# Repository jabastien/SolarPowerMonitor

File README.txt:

I'm building an Arduino Solar Power Monitor for my small home solar power system. At this point, I have 245 watts of solar panels.

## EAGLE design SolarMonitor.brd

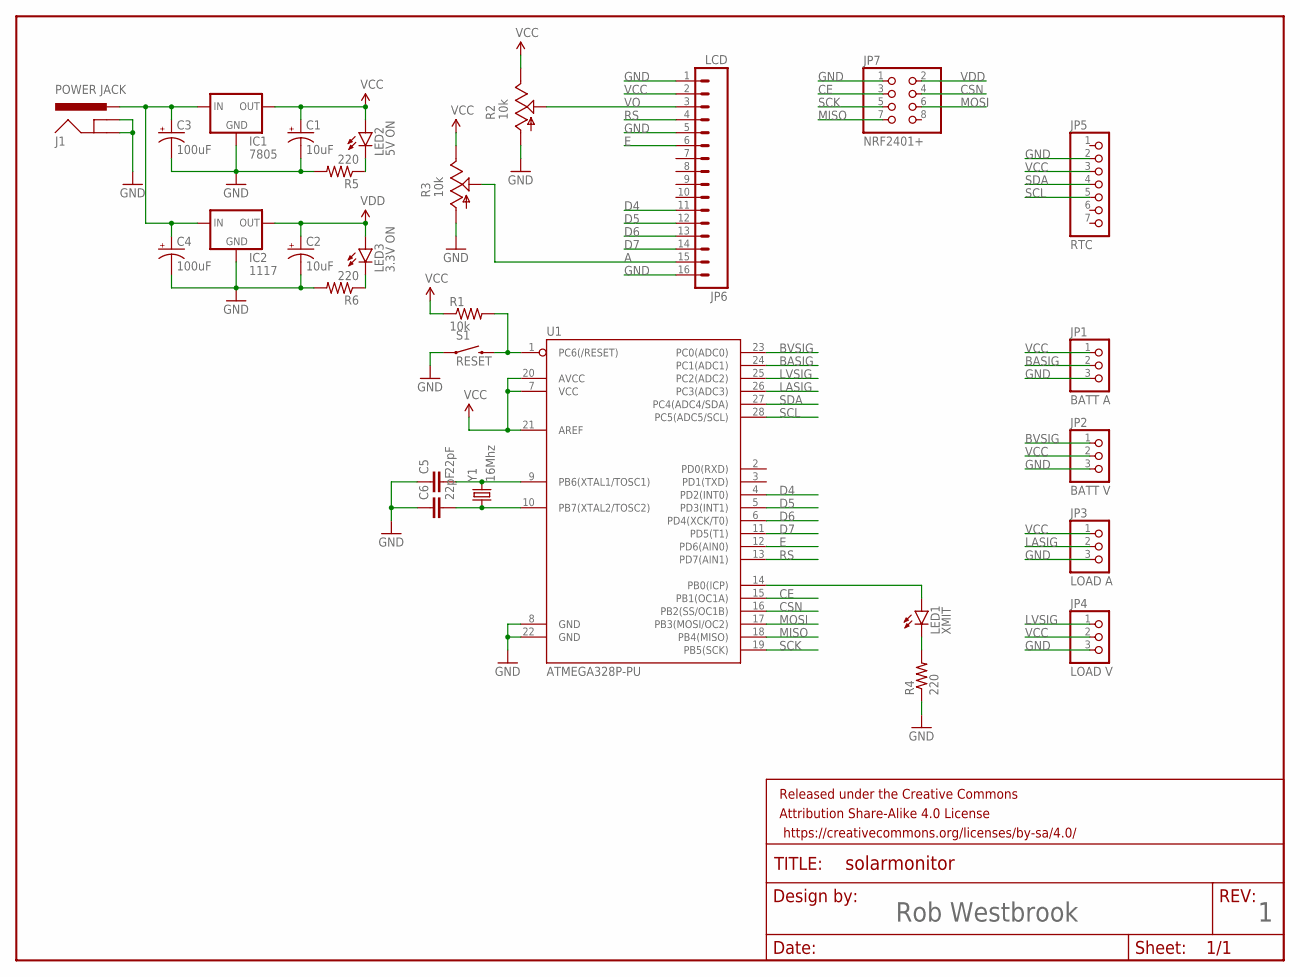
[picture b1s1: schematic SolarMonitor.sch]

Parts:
C1, C2: 10uF; CPOL-RADIAL-100UF-25V
C3, C4: 100uF; CPOL-RADIAL-10UF-25V
C5, C6: 22pF; CAP-PTH-SMALLEZ
FRAME1: FRAME-LETTER; CREATIVE_COMMONS
IC1: 7805; TO-220-ALT
IC2: 1117; 78XXL
J1: POWER JACK; POWER_JACK_PTH
JP1: BATT A; 1X03
JP2: BATT V; 1X03
JP3: LOAD A; 1X03
JP4: LOAD V; 1X03
JP5: RTC; 1X07
JP6: LCD; 1X16_LOCK
JP7: NRF2401+; 2X04
LED1: XMIT; LED5MM
LED2: 5V ON; LED5MM
LED3: 3.3V ON; LED5MM
R1: 10k; AXIAL-0.4
R2, R3: 10k; S64W
R4, R5, R6: 220; AXIAL-0.4
S1: RESET; TACTILE-PTH
U1: ATMEGA328P-PU; DIL28-3
Y1: 16Mhz; HC49US

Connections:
A: JP6.15, R3.S
BASIG: JP1.2, U1.24 (PC1(ADC1))
BVSIG: JP2.1, U1.23 (PC0(ADC0))
CE: JP7.3, U1.15 (PB1(OC1A))
CSN: JP7.4, U1.16 (PB2(SS/OC1B))
D4: JP6.11, U1.4 (PD2(INT0))
D5: JP6.12, U1.5 (PD3(INT1))
D6: JP6.13, U1.6 (PD4(XCK/T0))
D7: JP6.14, U1.11 (PD5(T1))
E: JP6.6, U1.12 (PD6(AIN0))
GND: C1.2 (-), C2.2 (-), C3.2 (-), C4.2 (-), C5.1, C6.1, IC1.GND, IC2.IN (GND), J1.GND, J1.GNDBREAK, JP1.3, JP2.3, JP3.3, JP4.3, JP5.2, JP6.1, JP6.5, JP6.16, JP7.1, R2.A, R3.A, R4.P$1 (1), R5.P$2 (2), R6.P$2 (2), S1.1, U1.8 (GND), U1.22 (GND)
LASIG: JP3.2, U1.26 (PC3(ADC3))
LVSIG: JP4.1, U1.25 (PC2(ADC2))
MISO: JP7.7, U1.18 (PB4(MISO))
MOSI: JP7.6, U1.17 (PB3(MOSI/OC2))
unnamed: C3.1 (+), C4.1 (+), IC1.IN, IC2.OUT (IN), J1.PWR
unnamed: C5.2, U1.9 (PB6(XTAL1/TOSC1)), Y1.2
unnamed: C6.2, U1.10 (PB7(XTAL2/TOSC2)), Y1.1
unnamed: LED1.A, U1.14 (PB0(ICP))
unnamed: LED1.K (C), R4.P$2 (2)
unnamed: R1.P$2 (2), S1.3 (2), U1.1 (PC6(/RESET))
unnamed: LED3.K (C), R6.P$1 (1)
unnamed: LED2.K (C), R5.P$1 (1)
RS: JP6.4, U1.13 (PD7(AIN1))
SCK: JP7.5, U1.19 (PB5(SCK))
SCL: JP5.5, U1.28 (PC5(ADC5/SCL))
SDA: JP5.4, U1.27 (PC4(ADC4/SDA))
VCC: C1.1 (+), IC1.OUT, JP1.1, JP2.2, JP3.1, JP4.2, JP5.3, JP6.2, LED2.A, R1.P$1 (1), R2.E, R3.E, U1.7 (VCC), U1.20 (AVCC), U1.21 (AREF)
VDD: C2.1 (+), IC2.GND (OUT), JP7.2, LED3.A
VO: JP6.3, R2.S

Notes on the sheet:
Rob Westbrook

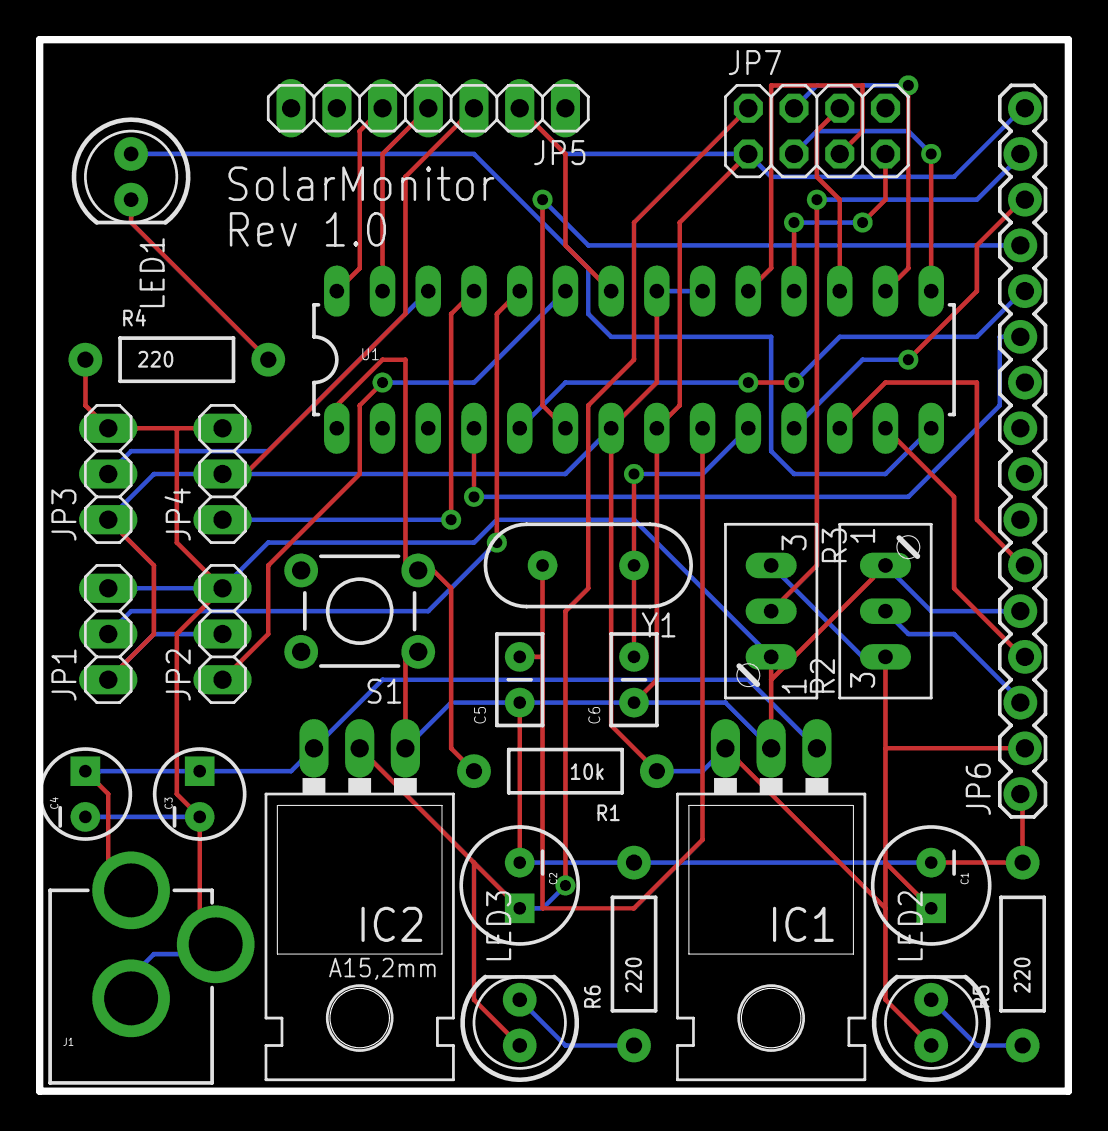
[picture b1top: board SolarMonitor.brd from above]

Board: 2 copper layers, 57.1 x 58.4 mm, 29 parts (0 on the bottom side), 30 nets.

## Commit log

2014-05-21 Initial commit.
2014-05-21 Inital commit
2014-05-21 Added "Arduino" to describe basis for monitor.
2014-05-21 Moved voltage offest into voltage read sensor formula

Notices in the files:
parts and their libraries:
SparkFun-Connectors: Licensing: Creative Commons ShareAlike 4.0 International - https://creativecommons.org/licenses/by-sa/4.0
SparkFun-Aesthetics: Released under the Creative Commons Attribution Share-Alike 4.0 License
SparkFun-Aesthetics: https://creativecommons.org/licenses/by-sa/4.0
